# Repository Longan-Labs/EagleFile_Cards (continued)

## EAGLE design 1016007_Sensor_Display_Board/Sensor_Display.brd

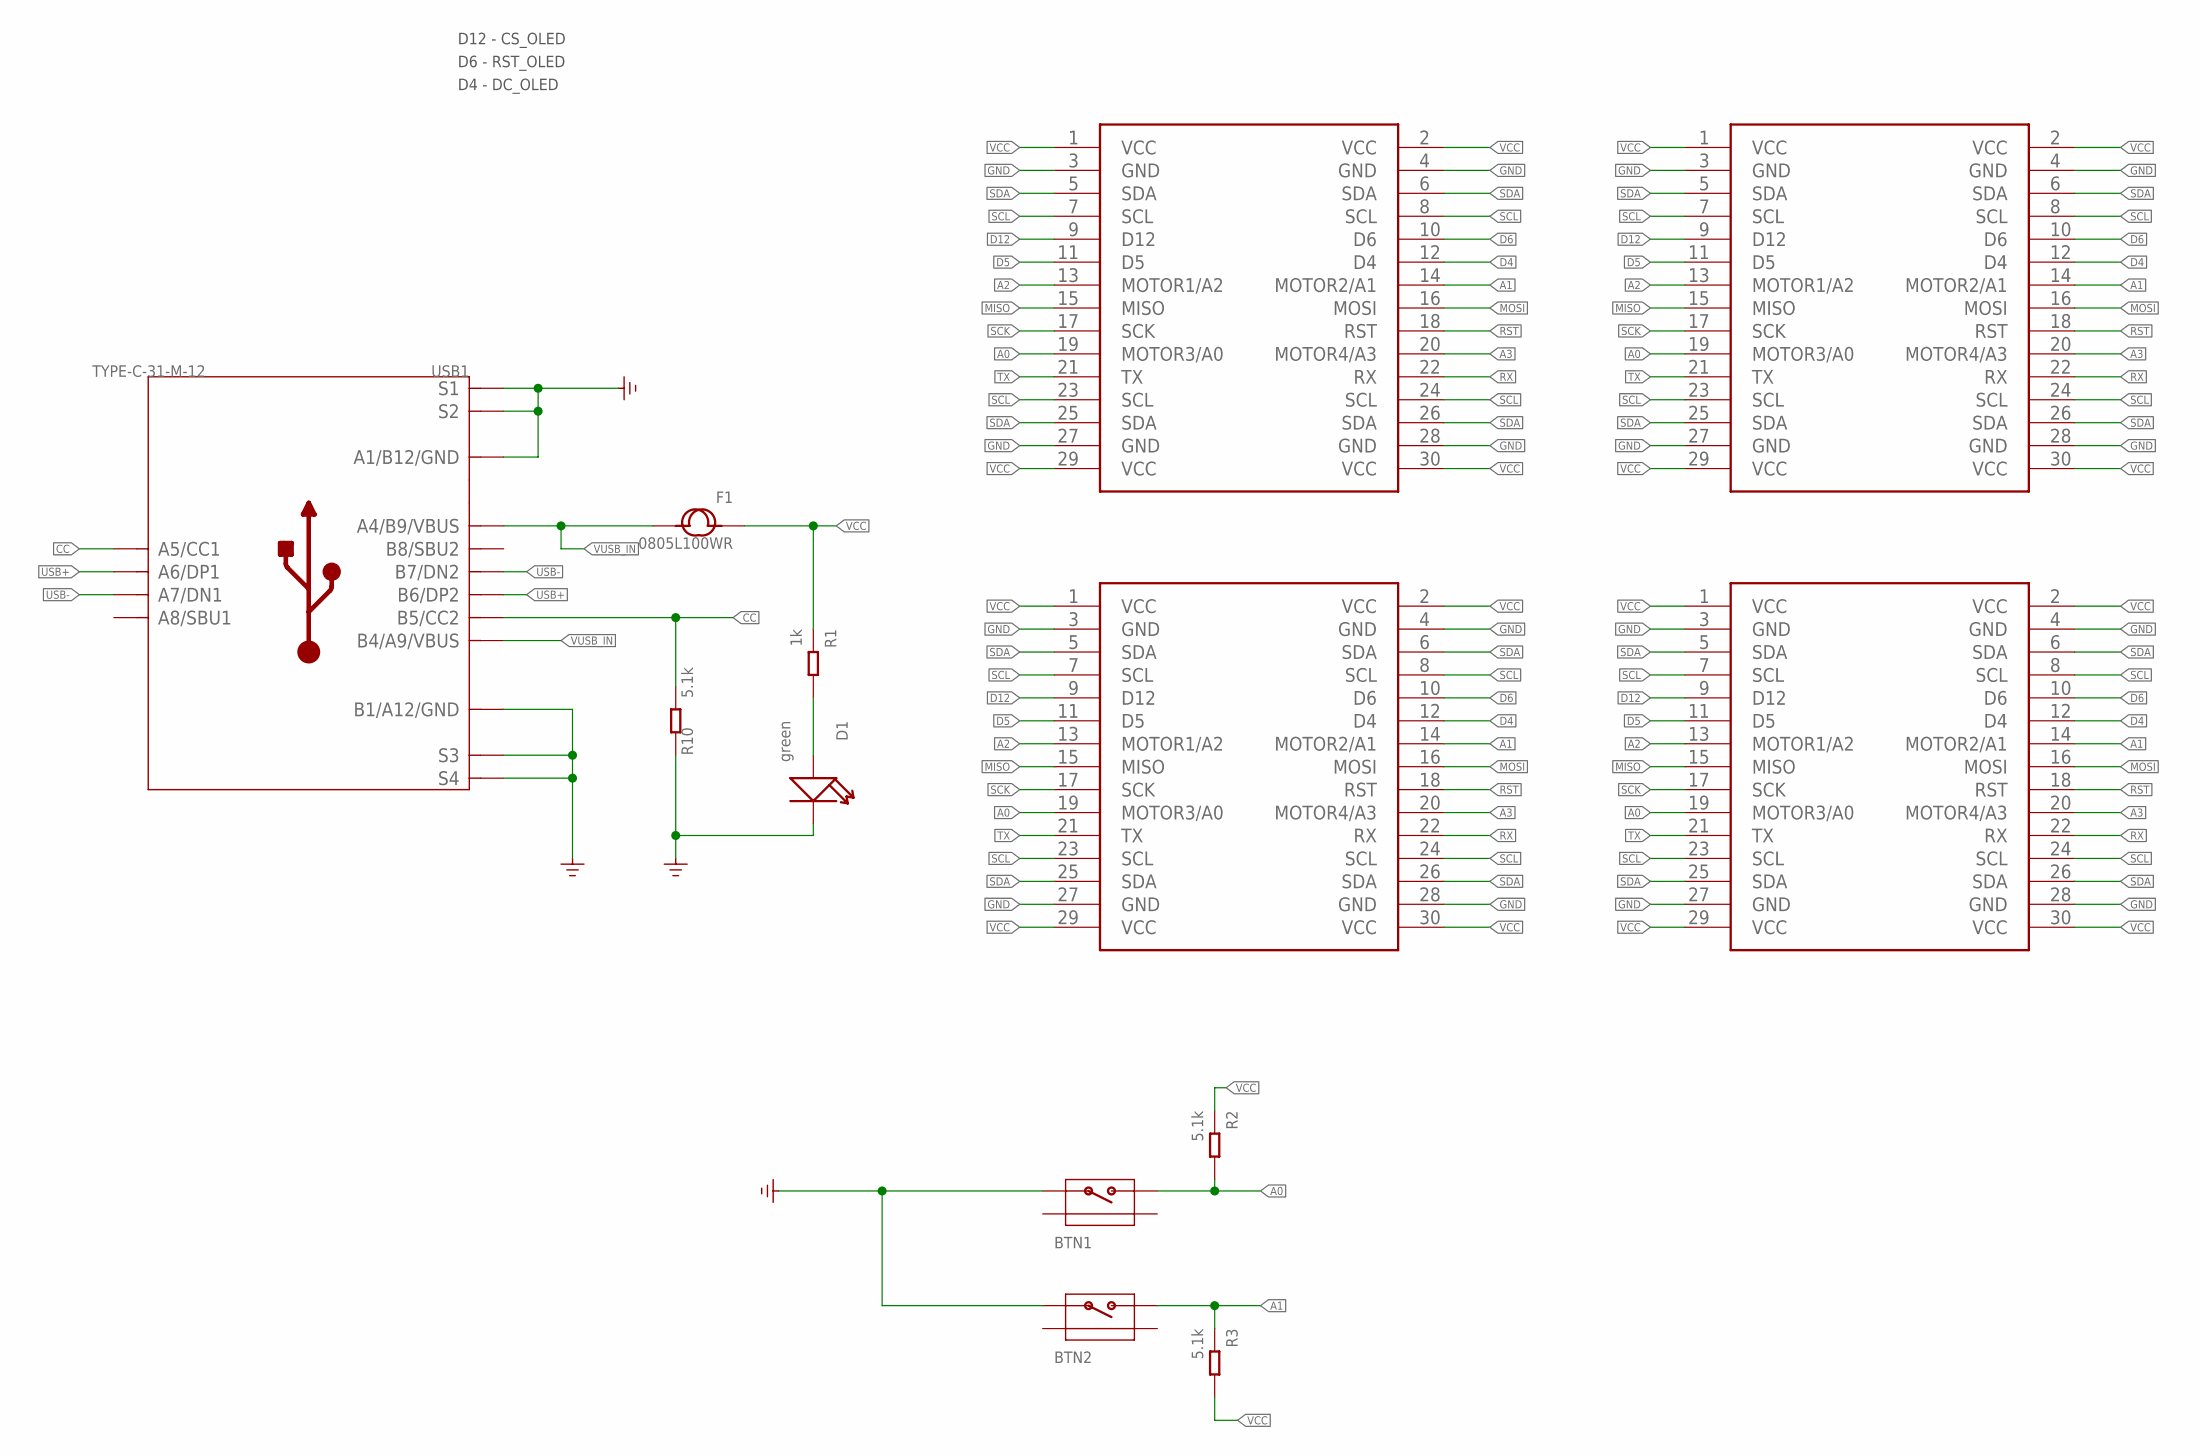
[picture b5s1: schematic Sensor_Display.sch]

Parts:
BTN1, BTN2: BUTTON-4P-REINFORCE'TS-1188E'; 4P-SMD-7X3.5X3.5H
D1: green; LED-0603
F1: 0805L100WR; F0805
MOUDLE1: MOUDLE-2X15P-2.54'90D'; 2X15P-2.54-90D
MOUDLE2, MOUDLE3, MOUDLE4: MOUDLE-2X15P-2.54'2.54'; 2X15P-2.54
R1: 1k; R0603
R2, R3, R10: 5.1k; R0603
USB1: TYPE-C-31-M-12; USB2.0-TYPE-C

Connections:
A0: BTN1.2, MOUDLE1.19 (MOTOR3/A0), MOUDLE2.19 (MOTOR3/A0), MOUDLE3.19 (MOTOR3/A0), MOUDLE4.19 (MOTOR3/A0), R2.2
A1: BTN2.2, MOUDLE1.14 (MOTOR2/A1), MOUDLE2.14 (MOTOR2/A1), MOUDLE3.14 (MOTOR2/A1), MOUDLE4.14 (MOTOR2/A1), R3.1
A2: MOUDLE1.13 (MOTOR1/A2), MOUDLE2.13 (MOTOR1/A2), MOUDLE3.13 (MOTOR1/A2), MOUDLE4.13 (MOTOR1/A2)
A3: MOUDLE1.20 (MOTOR4/A3), MOUDLE2.20 (MOTOR4/A3), MOUDLE3.20 (MOTOR4/A3), MOUDLE4.20 (MOTOR4/A3)
CC: R10.2, USB1.A5 (A5/CC1), USB1.B5 (B5/CC2)
D4: MOUDLE1.12 (D4), MOUDLE2.12 (D4), MOUDLE3.12 (D4), MOUDLE4.12 (D4)
D5: MOUDLE1.11 (D5), MOUDLE2.11 (D5), MOUDLE3.11 (D5), MOUDLE4.11 (D5)
D6: MOUDLE1.10 (D6), MOUDLE2.10 (D6), MOUDLE3.10 (D6), MOUDLE4.10 (D6)
D12: MOUDLE1.9 (D12), MOUDLE2.9 (D12), MOUDLE3.9 (D12), MOUDLE4.9 (D12)
GND: BTN1.1, BTN2.1, D1.-, MOUDLE1.3 (GND), MOUDLE1.4 (GND), MOUDLE1.27 (GND), MOUDLE1.28 (GND), MOUDLE2.3 (GND), MOUDLE2.4 (GND), MOUDLE2.27 (GND), MOUDLE2.28 (GND), MOUDLE3.3 (GND), MOUDLE3.4 (GND), MOUDLE3.27 (GND), MOUDLE3.28 (GND), MOUDLE4.3 (GND), MOUDLE4.4 (GND), MOUDLE4.27 (GND), MOUDLE4.28 (GND), R10.1, USB1.A1_B12 (A1/B12/GND), USB1.B1_A12 (B1/A12/GND), USB1.S1, USB1.S2, USB1.S3, USB1.S4, USB1.S5 (S1), USB1.S6 (S2)
MISO: MOUDLE1.15 (MISO), MOUDLE2.15 (MISO), MOUDLE3.15 (MISO), MOUDLE4.15 (MISO)
MOSI: MOUDLE1.16 (MOSI), MOUDLE2.16 (MOSI), MOUDLE3.16 (MOSI), MOUDLE4.16 (MOSI)
unnamed: D1.+, R1.2
RST: MOUDLE1.18 (RST), MOUDLE2.18 (RST), MOUDLE3.18 (RST), MOUDLE4.18 (RST)
RX: MOUDLE1.22 (RX), MOUDLE2.22 (RX), MOUDLE3.22 (RX), MOUDLE4.22 (RX)
SCK: MOUDLE1.17 (SCK), MOUDLE2.17 (SCK), MOUDLE3.17 (SCK), MOUDLE4.17 (SCK)
SCL: MOUDLE1.7 (SCL), MOUDLE1.8 (SCL), MOUDLE1.23 (SCL), MOUDLE1.24 (SCL), MOUDLE2.7 (SCL), MOUDLE2.8 (SCL), MOUDLE2.23 (SCL), MOUDLE2.24 (SCL), MOUDLE3.7 (SCL), MOUDLE3.8 (SCL), MOUDLE3.23 (SCL), MOUDLE3.24 (SCL), MOUDLE4.7 (SCL), MOUDLE4.8 (SCL), MOUDLE4.23 (SCL), MOUDLE4.24 (SCL)
SDA: MOUDLE1.5 (SDA), MOUDLE1.6 (SDA), MOUDLE1.25 (SDA), MOUDLE1.26 (SDA), MOUDLE2.5 (SDA), MOUDLE2.6 (SDA), MOUDLE2.25 (SDA), MOUDLE2.26 (SDA), MOUDLE3.5 (SDA), MOUDLE3.6 (SDA), MOUDLE3.25 (SDA), MOUDLE3.26 (SDA), MOUDLE4.5 (SDA), MOUDLE4.6 (SDA), MOUDLE4.25 (SDA), MOUDLE4.26 (SDA)
TX: MOUDLE1.21 (TX), MOUDLE2.21 (TX), MOUDLE3.21 (TX), MOUDLE4.21 (TX)
USB+: USB1.A6 (A6/DP1), USB1.B6 (B6/DP2)
USB-: USB1.A7 (A7/DN1), USB1.B7 (B7/DN2)
VCC: F1.1, MOUDLE1.1 (VCC), MOUDLE1.2 (VCC), MOUDLE1.29 (VCC), MOUDLE1.30 (VCC), MOUDLE2.1 (VCC), MOUDLE2.2 (VCC), MOUDLE2.29 (VCC), MOUDLE2.30 (VCC), MOUDLE3.1 (VCC), MOUDLE3.2 (VCC), MOUDLE3.29 (VCC), MOUDLE3.30 (VCC), MOUDLE4.1 (VCC), MOUDLE4.2 (VCC), MOUDLE4.29 (VCC), MOUDLE4.30 (VCC), R1.1, R2.1, R3.2
VUSB_IN: F1.2, USB1.A4_B9 (A4/B9/VBUS), USB1.B4_A9 (B4/A9/VBUS)

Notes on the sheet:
D12 - CS_OLED
D6 - RST_OLED
D4 - DC_OLED

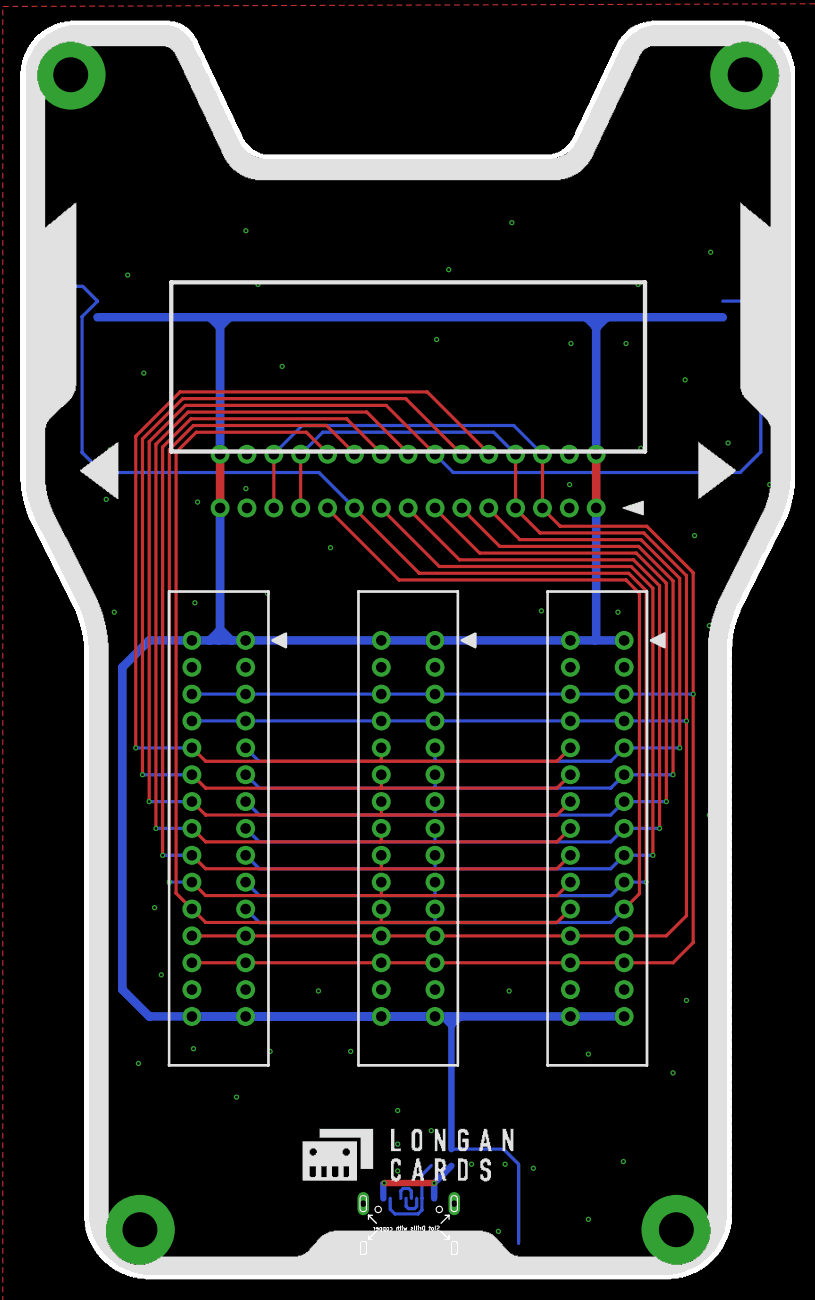
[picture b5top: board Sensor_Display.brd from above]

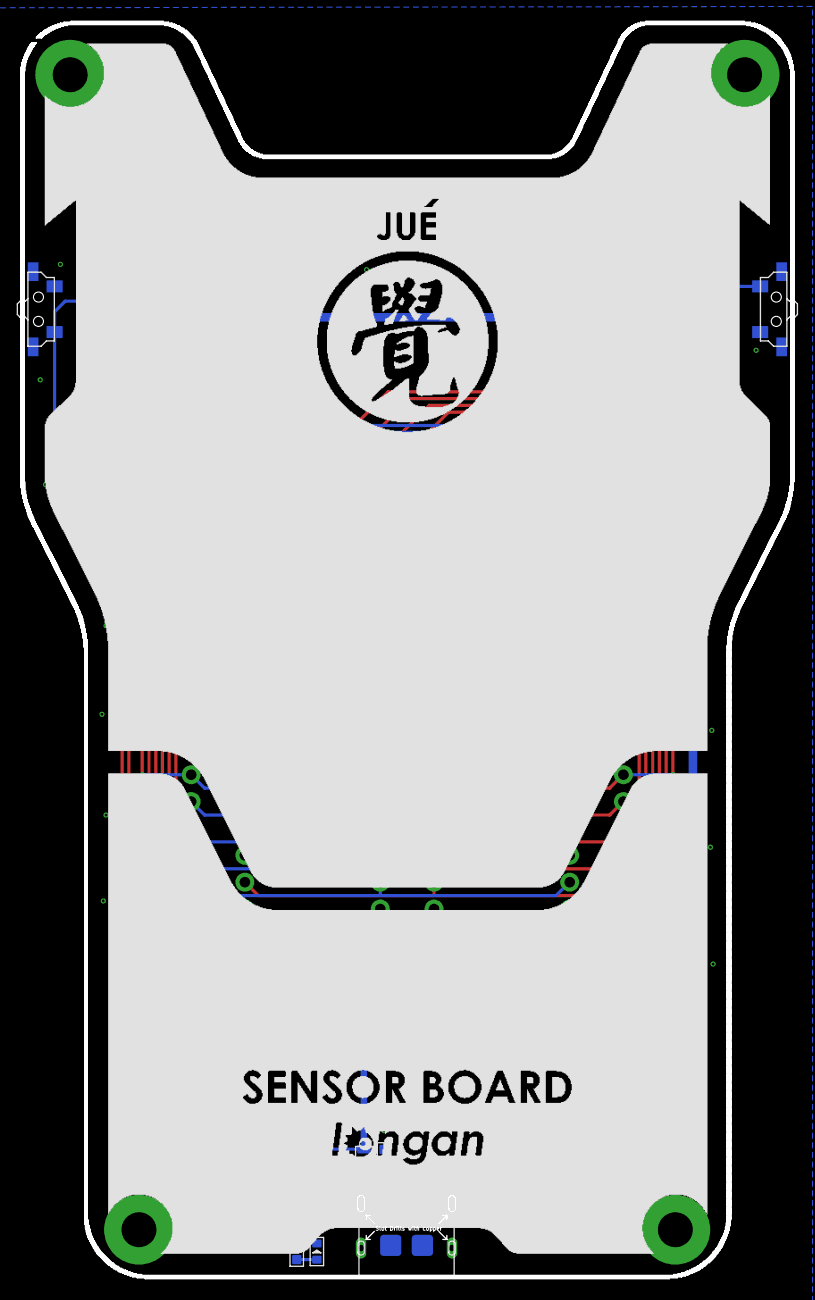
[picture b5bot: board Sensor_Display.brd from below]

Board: 2 copper layers, 73.1 x 118.9 mm, 13 parts (9 on the bottom side), 23 nets.

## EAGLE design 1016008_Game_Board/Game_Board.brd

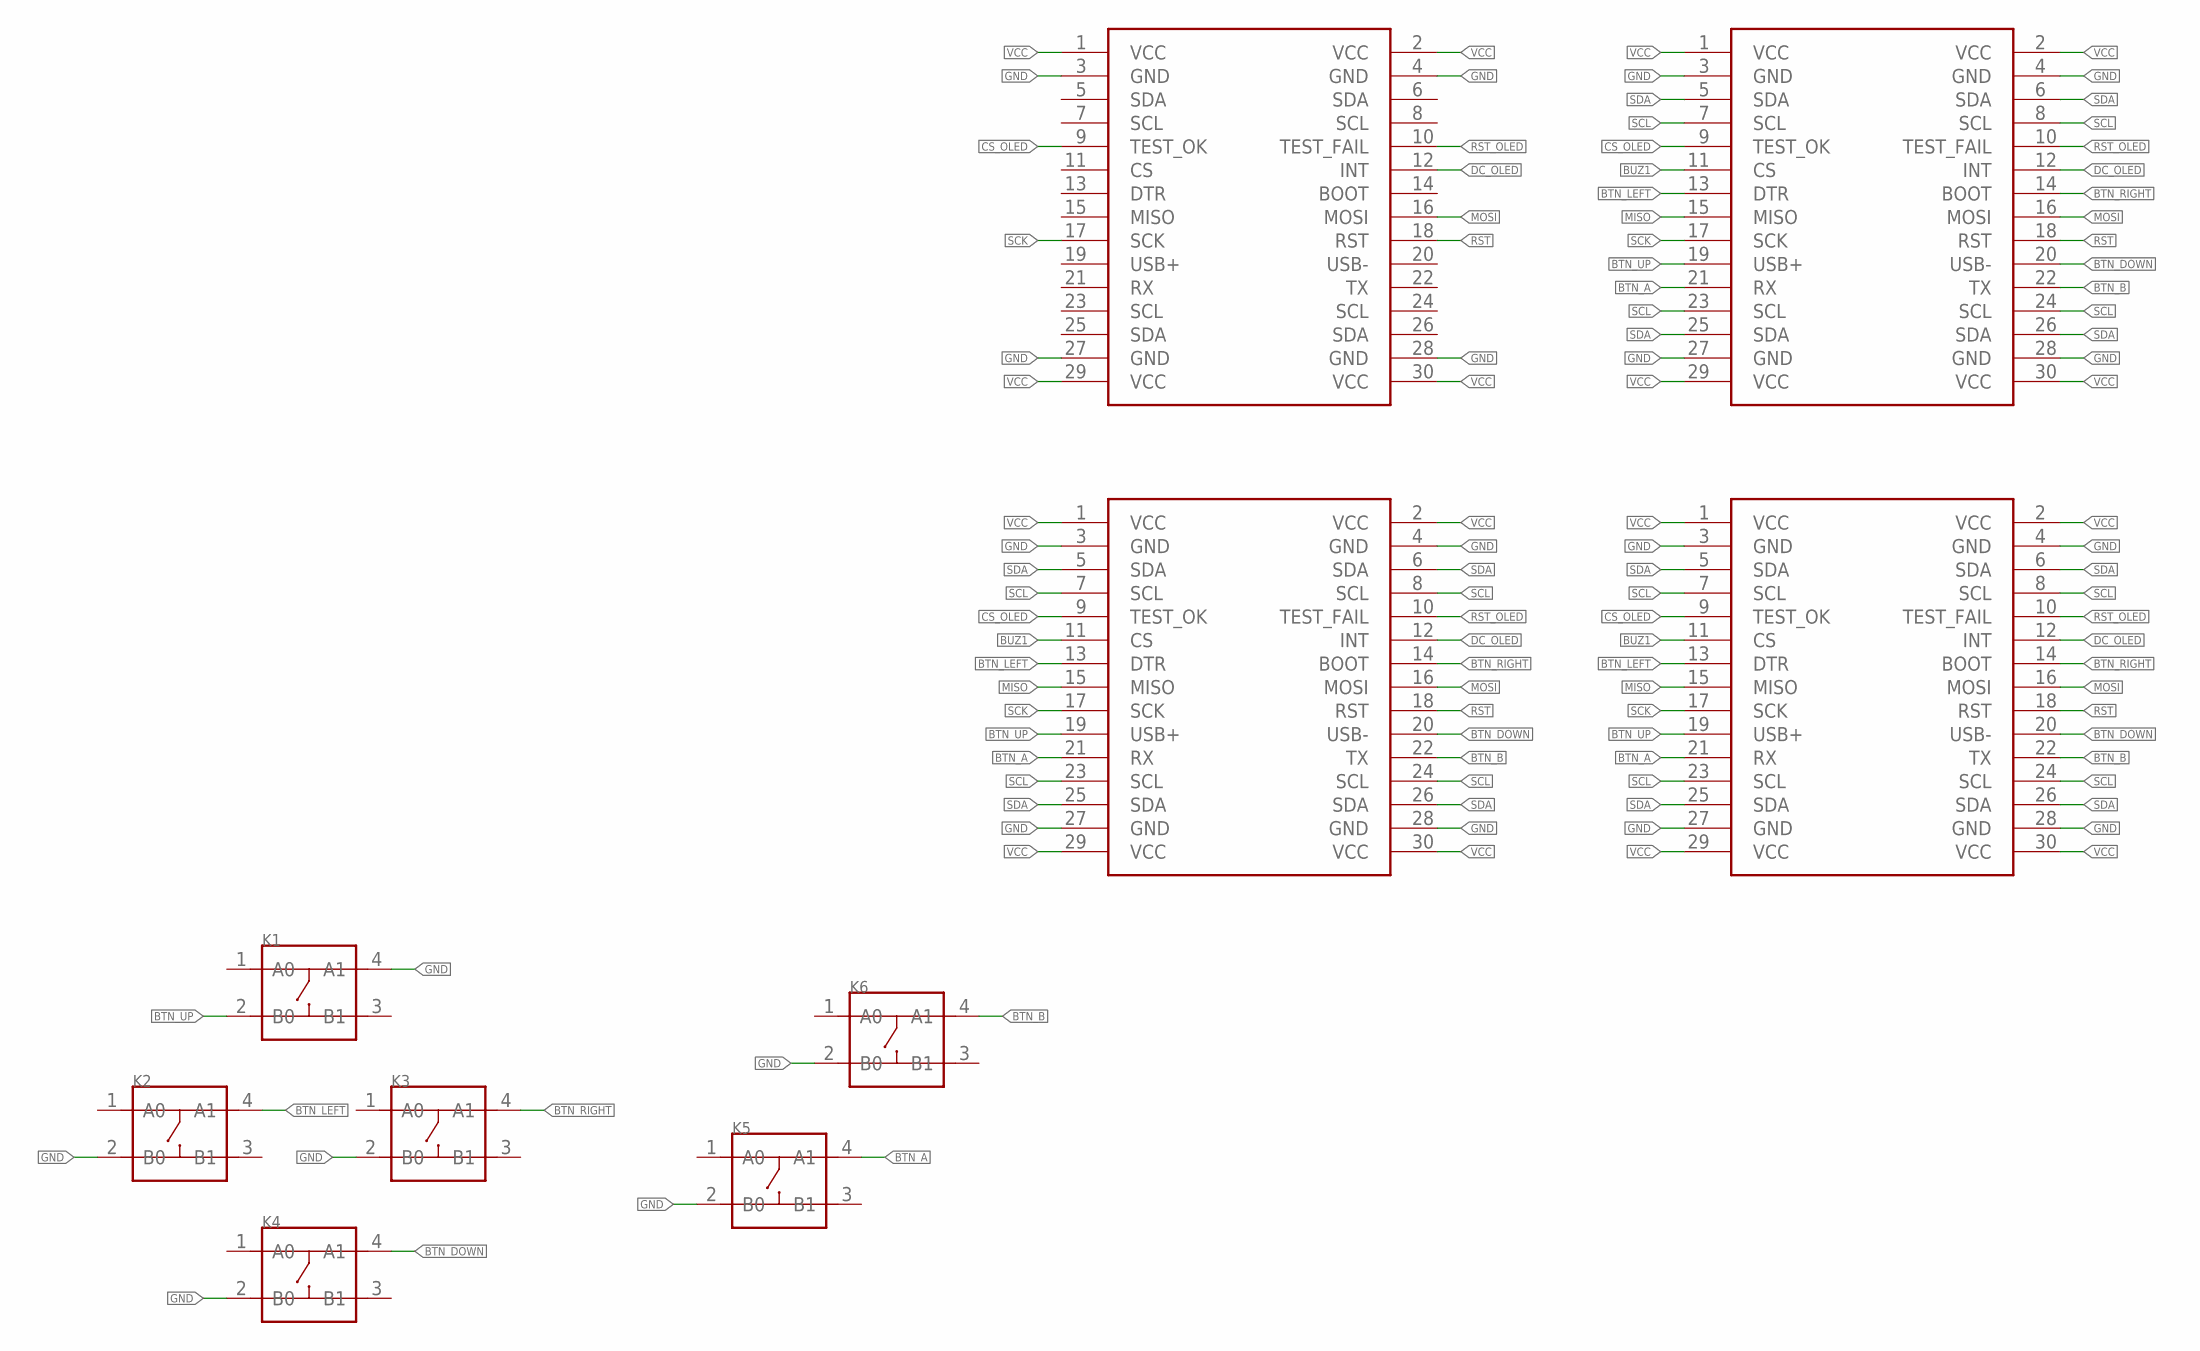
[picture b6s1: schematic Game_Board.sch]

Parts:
K1, K2, K3, K4, K5, K6: BUTTON-4PDTSM-62K-S-V-T/R(SN431); SW4-SMD-6.0X6.0X5.0MM
MOUDLE1, MOUDLE2, MOUDLE4: MOUDLE-2X15P-2.54'2.54'; 2X15P-2.54
MOUDLE3: MOUDLE-2X15P-2.54'90D'; 2X15P-2.54-90D

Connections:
BTN_A: K5.4 (A1), MOUDLE1.21 (RX), MOUDLE2.21 (RX), MOUDLE4.21 (RX)
BTN_B: K6.4 (A1), MOUDLE1.22 (TX), MOUDLE2.22 (TX), MOUDLE4.22 (TX)
BTN_DOWN: K4.4 (A1), MOUDLE1.20 (USB-), MOUDLE2.20 (USB-), MOUDLE4.20 (USB-)
BTN_LEFT: K2.4 (A1), MOUDLE1.13 (DTR), MOUDLE2.13 (DTR), MOUDLE4.13 (DTR)
BTN_RIGHT: K3.4 (A1), MOUDLE1.14 (BOOT), MOUDLE2.14 (BOOT), MOUDLE4.14 (BOOT)
BTN_UP: K1.2 (B0), MOUDLE1.19 (USB+), MOUDLE2.19 (USB+), MOUDLE4.19 (USB+)
BUZ1: MOUDLE1.11 (CS), MOUDLE2.11 (CS), MOUDLE4.11 (CS)
CS_OLED: MOUDLE1.9 (TEST_OK), MOUDLE2.9 (TEST_OK), MOUDLE3.9 (TEST_OK), MOUDLE4.9 (TEST_OK)
DC_OLED: MOUDLE1.12 (INT), MOUDLE2.12 (INT), MOUDLE3.12 (INT), MOUDLE4.12 (INT)
GND: K1.4 (A1), K2.2 (B0), K3.2 (B0), K4.2 (B0), K5.2 (B0), K6.2 (B0), MOUDLE1.3 (GND), MOUDLE1.4 (GND), MOUDLE1.27 (GND), MOUDLE1.28 (GND), MOUDLE2.3 (GND), MOUDLE2.4 (GND), MOUDLE2.27 (GND), MOUDLE2.28 (GND), MOUDLE3.3 (GND), MOUDLE3.4 (GND), MOUDLE3.27 (GND), MOUDLE3.28 (GND), MOUDLE4.3 (GND), MOUDLE4.4 (GND), MOUDLE4.27 (GND), MOUDLE4.28 (GND)
MISO: MOUDLE1.15 (MISO), MOUDLE2.15 (MISO), MOUDLE4.15 (MISO)
MOSI: MOUDLE1.16 (MOSI), MOUDLE2.16 (MOSI), MOUDLE3.16 (MOSI), MOUDLE4.16 (MOSI)
RST: MOUDLE1.18 (RST), MOUDLE2.18 (RST), MOUDLE3.18 (RST), MOUDLE4.18 (RST)
RST_OLED: MOUDLE1.10 (TEST_FAIL), MOUDLE2.10 (TEST_FAIL), MOUDLE3.10 (TEST_FAIL), MOUDLE4.10 (TEST_FAIL)
SCK: MOUDLE1.17 (SCK), MOUDLE2.17 (SCK), MOUDLE3.17 (SCK), MOUDLE4.17 (SCK)
SCL: MOUDLE1.7 (SCL), MOUDLE1.8 (SCL), MOUDLE1.23 (SCL), MOUDLE1.24 (SCL), MOUDLE2.7 (SCL), MOUDLE2.8 (SCL), MOUDLE2.23 (SCL), MOUDLE2.24 (SCL), MOUDLE4.7 (SCL), MOUDLE4.8 (SCL), MOUDLE4.23 (SCL), MOUDLE4.24 (SCL)
SDA: MOUDLE1.5 (SDA), MOUDLE1.6 (SDA), MOUDLE1.25 (SDA), MOUDLE1.26 (SDA), MOUDLE2.5 (SDA), MOUDLE2.6 (SDA), MOUDLE2.25 (SDA), MOUDLE2.26 (SDA), MOUDLE4.5 (SDA), MOUDLE4.6 (SDA), MOUDLE4.25 (SDA), MOUDLE4.26 (SDA)
VCC: MOUDLE1.1 (VCC), MOUDLE1.2 (VCC), MOUDLE1.29 (VCC), MOUDLE1.30 (VCC), MOUDLE2.1 (VCC), MOUDLE2.2 (VCC), MOUDLE2.29 (VCC), MOUDLE2.30 (VCC), MOUDLE3.1 (VCC), MOUDLE3.2 (VCC), MOUDLE3.29 (VCC), MOUDLE3.30 (VCC), MOUDLE4.1 (VCC), MOUDLE4.2 (VCC), MOUDLE4.29 (VCC), MOUDLE4.30 (VCC)

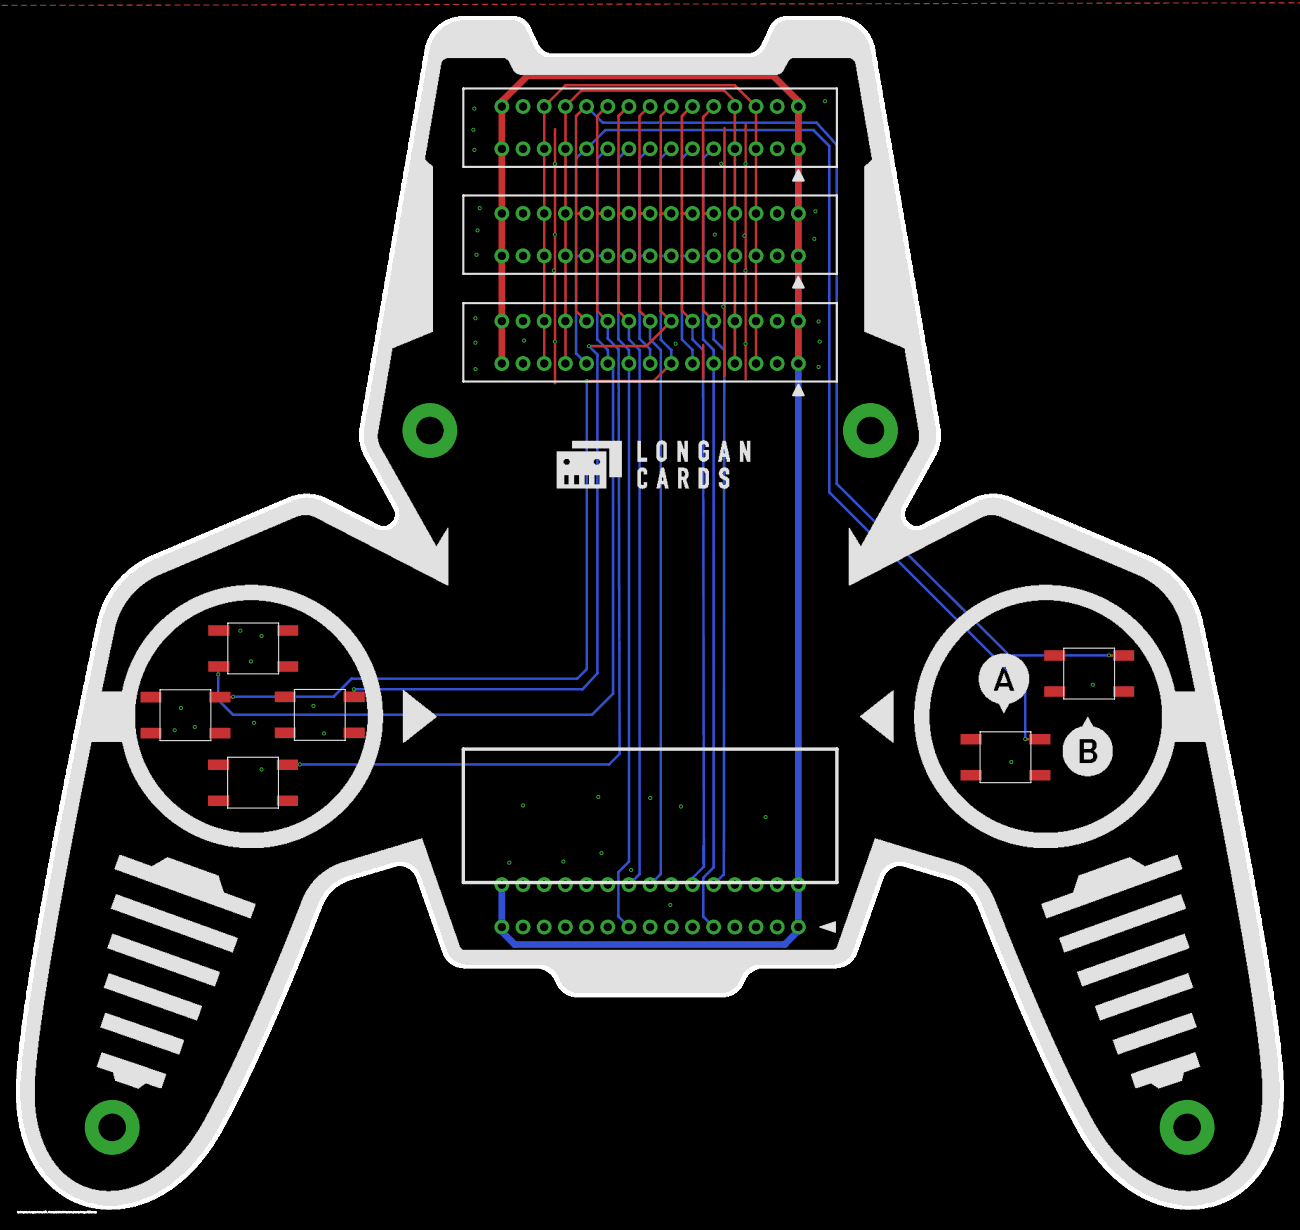
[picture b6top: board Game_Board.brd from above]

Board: 2 copper layers, 151.9 x 143.0 mm, 10 parts (0 on the bottom side), 18 nets.

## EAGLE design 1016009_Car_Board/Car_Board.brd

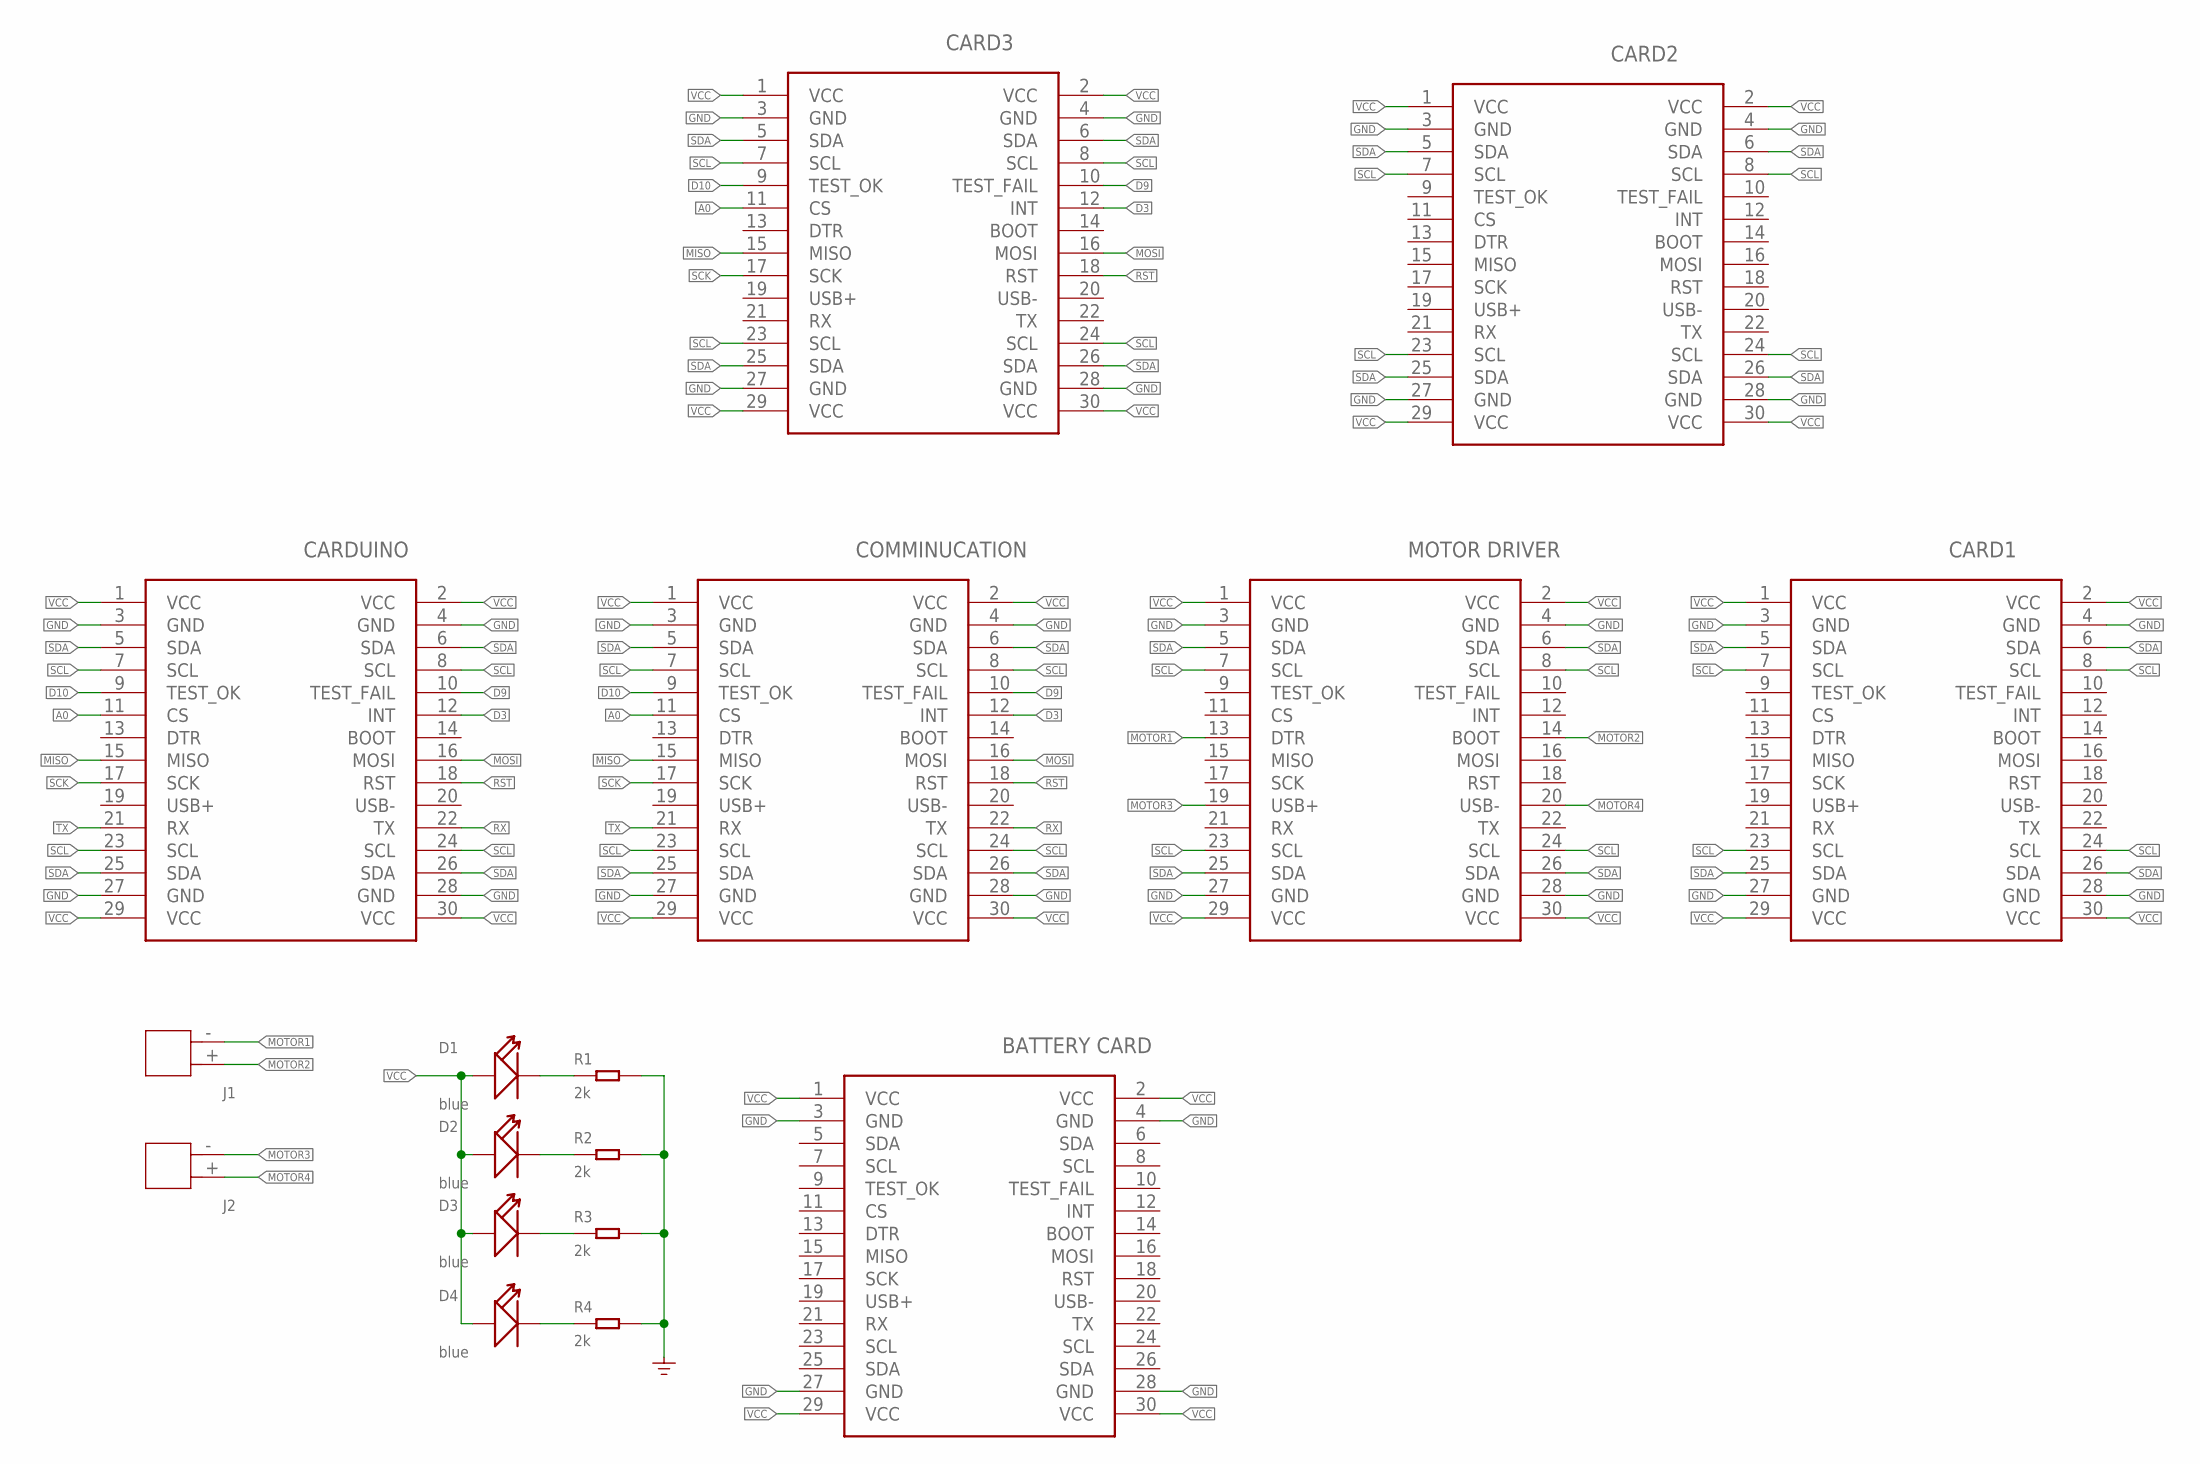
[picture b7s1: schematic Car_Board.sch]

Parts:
CARDUINO: CARDUINO; 2X15P-2.54
CARDUINO1: COMMINUCATION; 2X15P-2.54
CARDUINO2: MOTOR DRIVER; 2X15P-2.54
CARDUINO3: CARD1; 2X15P-2.54
CARDUINO4: CARD2; 2X15P-2.54
CARDUINO5: CARD3; 2X15P-2.54-90D
D1, D2, D3, D4: blue; LED-0603
J1, J2: JST-2P-DIP'2.0'; H2-2.0-6X4.5MM
MOUDLE4: BATTERY CARD; 2X15P-2.54
R1, R2, R3, R4: 2k; R0603

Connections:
A0: CARDUINO.11 (CS), CARDUINO1.11 (CS), CARDUINO5.11 (CS)
D3: CARDUINO.12 (INT), CARDUINO1.12 (INT), CARDUINO5.12 (INT)
D9: CARDUINO.10 (TEST_FAIL), CARDUINO1.10 (TEST_FAIL), CARDUINO5.10 (TEST_FAIL)
D10: CARDUINO.9 (TEST_OK), CARDUINO1.9 (TEST_OK), CARDUINO5.9 (TEST_OK)
GND: CARDUINO.3 (GND), CARDUINO.4 (GND), CARDUINO.27 (GND), CARDUINO.28 (GND), CARDUINO1.3 (GND), CARDUINO1.4 (GND), CARDUINO1.27 (GND), CARDUINO1.28 (GND), CARDUINO2.3 (GND), CARDUINO2.4 (GND), CARDUINO2.27 (GND), CARDUINO2.28 (GND), CARDUINO3.3 (GND), CARDUINO3.4 (GND), CARDUINO3.27 (GND), CARDUINO3.28 (GND), CARDUINO4.3 (GND), CARDUINO4.4 (GND), CARDUINO4.27 (GND), CARDUINO4.28 (GND), CARDUINO5.3 (GND), CARDUINO5.4 (GND), CARDUINO5.27 (GND), CARDUINO5.28 (GND), MOUDLE4.3 (GND), MOUDLE4.4 (GND), MOUDLE4.27 (GND), MOUDLE4.28 (GND), R1.2, R2.2, R3.2, R4.2
MISO: CARDUINO.15 (MISO), CARDUINO1.15 (MISO), CARDUINO5.15 (MISO)
MOSI: CARDUINO.16 (MOSI), CARDUINO1.16 (MOSI), CARDUINO5.16 (MOSI)
MOTOR1: CARDUINO2.13 (DTR), J1.-
MOTOR2: CARDUINO2.14 (BOOT), J1.+
MOTOR3: CARDUINO2.19 (USB+), J2.-
MOTOR4: CARDUINO2.20 (USB-), J2.+
unnamed: D1.-, R1.1
unnamed: D2.-, R2.1
unnamed: D3.-, R3.1
unnamed: D4.-, R4.1
RST: CARDUINO.18 (RST), CARDUINO1.18 (RST), CARDUINO5.18 (RST)
RX: CARDUINO.22 (TX), CARDUINO1.22 (TX)
SCK: CARDUINO.17 (SCK), CARDUINO1.17 (SCK), CARDUINO5.17 (SCK)
SCL: CARDUINO.7 (SCL), CARDUINO.8 (SCL), CARDUINO.23 (SCL), CARDUINO.24 (SCL), CARDUINO1.7 (SCL), CARDUINO1.8 (SCL), CARDUINO1.23 (SCL), CARDUINO1.24 (SCL), CARDUINO2.7 (SCL), CARDUINO2.8 (SCL), CARDUINO2.23 (SCL), CARDUINO2.24 (SCL), CARDUINO3.7 (SCL), CARDUINO3.8 (SCL), CARDUINO3.23 (SCL), CARDUINO3.24 (SCL), CARDUINO4.7 (SCL), CARDUINO4.8 (SCL), CARDUINO4.23 (SCL), CARDUINO4.24 (SCL), CARDUINO5.7 (SCL), CARDUINO5.8 (SCL), CARDUINO5.23 (SCL), CARDUINO5.24 (SCL)
SDA: CARDUINO.5 (SDA), CARDUINO.6 (SDA), CARDUINO.25 (SDA), CARDUINO.26 (SDA), CARDUINO1.5 (SDA), CARDUINO1.6 (SDA), CARDUINO1.25 (SDA), CARDUINO1.26 (SDA), CARDUINO2.5 (SDA), CARDUINO2.6 (SDA), CARDUINO2.25 (SDA), CARDUINO2.26 (SDA), CARDUINO3.5 (SDA), CARDUINO3.6 (SDA), CARDUINO3.25 (SDA), CARDUINO3.26 (SDA), CARDUINO4.5 (SDA), CARDUINO4.6 (SDA), CARDUINO4.25 (SDA), CARDUINO4.26 (SDA), CARDUINO5.5 (SDA), CARDUINO5.6 (SDA), CARDUINO5.25 (SDA), CARDUINO5.26 (SDA)
TX: CARDUINO.21 (RX), CARDUINO1.21 (RX)
VCC: CARDUINO.1 (VCC), CARDUINO.2 (VCC), CARDUINO.29 (VCC), CARDUINO.30 (VCC), CARDUINO1.1 (VCC), CARDUINO1.2 (VCC), CARDUINO1.29 (VCC), CARDUINO1.30 (VCC), CARDUINO2.1 (VCC), CARDUINO2.2 (VCC), CARDUINO2.29 (VCC), CARDUINO2.30 (VCC), CARDUINO3.1 (VCC), CARDUINO3.2 (VCC), CARDUINO3.29 (VCC), CARDUINO3.30 (VCC), CARDUINO4.1 (VCC), CARDUINO4.2 (VCC), CARDUINO4.29 (VCC), CARDUINO4.30 (VCC), CARDUINO5.1 (VCC), CARDUINO5.2 (VCC), CARDUINO5.29 (VCC), CARDUINO5.30 (VCC), D1.+, D2.+, D3.+, D4.+, MOUDLE4.1 (VCC), MOUDLE4.2 (VCC), MOUDLE4.29 (VCC), MOUDLE4.30 (VCC)

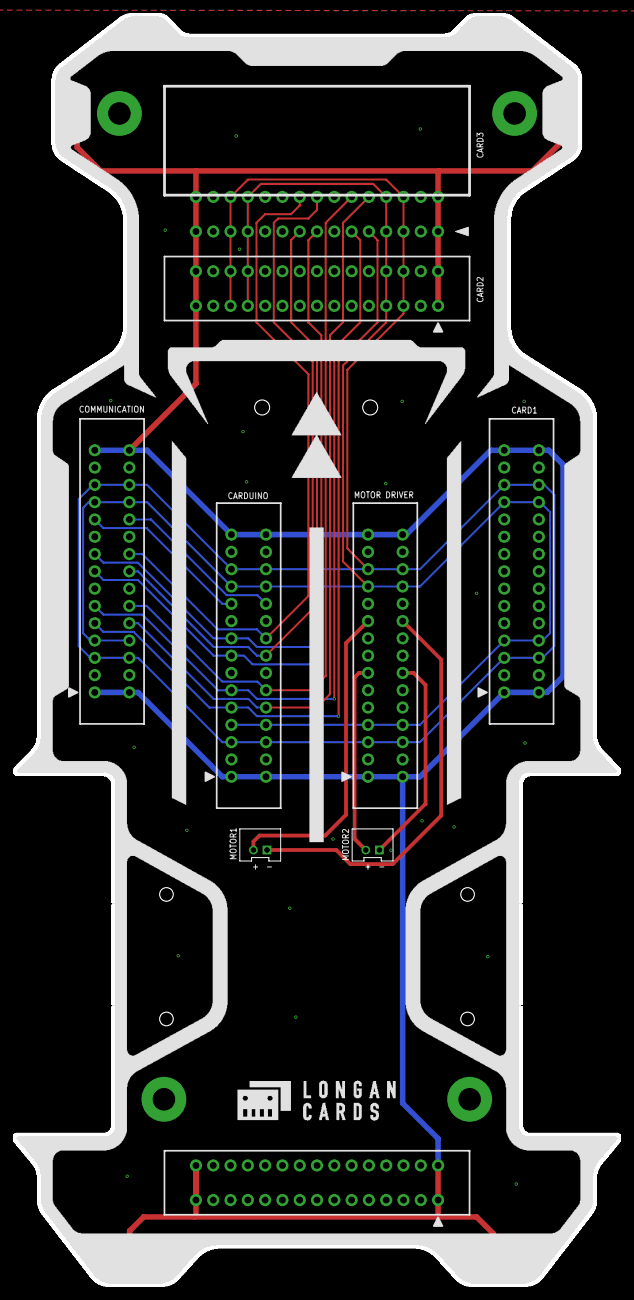
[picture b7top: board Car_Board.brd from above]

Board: 2 copper layers, 89.1 x 186.9 mm, 17 parts (0 on the bottom side), 22 nets.
